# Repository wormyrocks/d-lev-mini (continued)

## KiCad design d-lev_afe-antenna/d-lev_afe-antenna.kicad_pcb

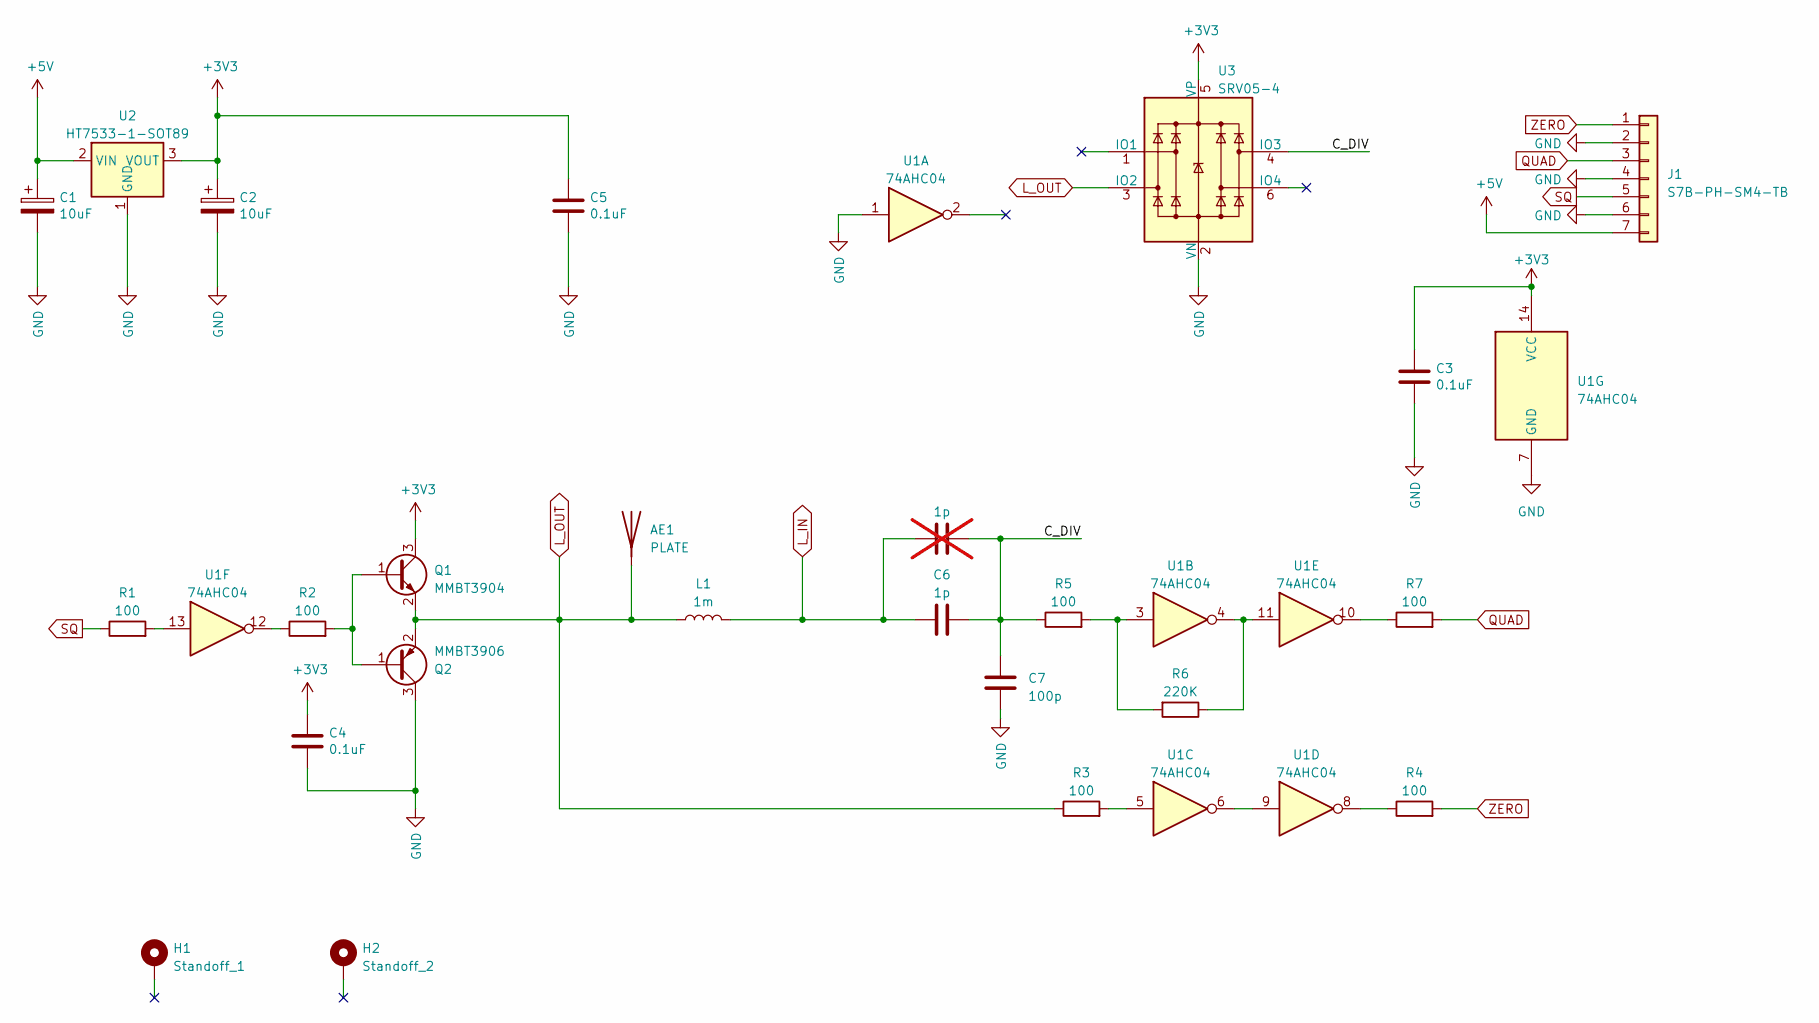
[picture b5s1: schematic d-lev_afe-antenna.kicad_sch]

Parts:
AE1: PLATE
C1, C2: 10uF; CP_EIA-3216-18_Kemet-A
C3, C4, C5: 0.1uF; C_0603_1608Metric
C6: 1p; C_0603_1608Metric
C7: 100p; C_0603_1608Metric
C8: 1p; C_0805_2012Metric_Pad1.18x1.45mm_HandSolder; not fitted
H1: Standoff_1; SMTSO-M4
H2: Standoff_2; SMTSO-M4
J1: S7B-PH-SM4-TB; JST_PH_S7B-PH-SM4-TB_1x07-1MP_P2.00mm_Horizontal
L1: 1m; LargeHoneycombCoil
Q1: MMBT3904; SOT-23
Q2: MMBT3906; SOT-23
R1, R2, R3, R4, R5, R7: 100; R_0603_1608Metric
R6: 220K; R_0603_1608Metric
U1: 74AHC04; SOIC-14_3.9x8.7mm_P1.27mm
U2: HT7533-1-SOT89; SOT-89-3
U3: SRV05-4; SOT-23-6

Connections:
+3V3: C2.1, C3.1, C4.1, C5.1, Q1.3 (C), U1.14 (VCC), U2.3 (VOUT), U3.5 (VP)
+5V: C1.1, J1.7, U2.2 (VIN)
/C_DIV: C6.2, C7.1, C8.2, R5.1, U3.4 (IO3)
GND: C1.2, C2.2, C3.2, C4.2, C5.2, C7.2, J1.2, J1.4, J1.6, Q2.3 (C), U1.1, U1.7 (GND), U2.1 (GND), U3.2 (VN)
L_IN: C6.1, C8.1, L1.2
L_OUT: AE1.1, L1.1, Q1.2 (E), Q2.2 (E), R3.1, U3.3 (IO2)
unnamed: Q1.1 (B), Q2.1 (B), R2.2
unnamed: R1.2, U1.13
unnamed: R2.1, U1.12
unnamed: R3.2, U1.5
unnamed: R4.1, U1.8
unnamed: R5.2, R6.2, U1.3
unnamed: R6.1, U1.4, U1.11
unnamed: R7.1, U1.10
unnamed: U1.6, U1.9
QUAD: J1.3, R7.2
SQ: J1.5, R1.1
ZERO: J1.1, R4.2

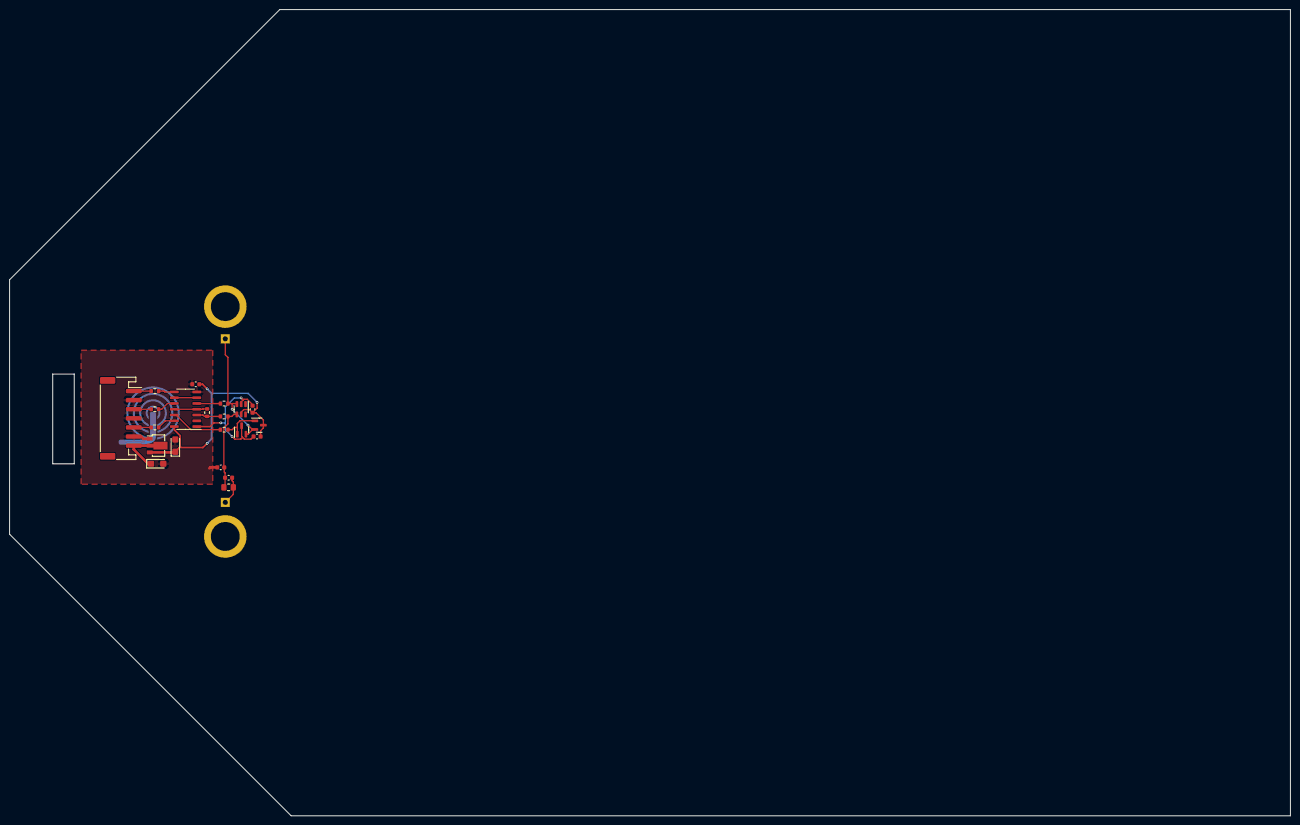
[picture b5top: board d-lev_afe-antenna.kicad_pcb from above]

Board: 2 copper layers, 282.0 x 177.5 mm, 24 parts (1 on the bottom side), 18 nets.

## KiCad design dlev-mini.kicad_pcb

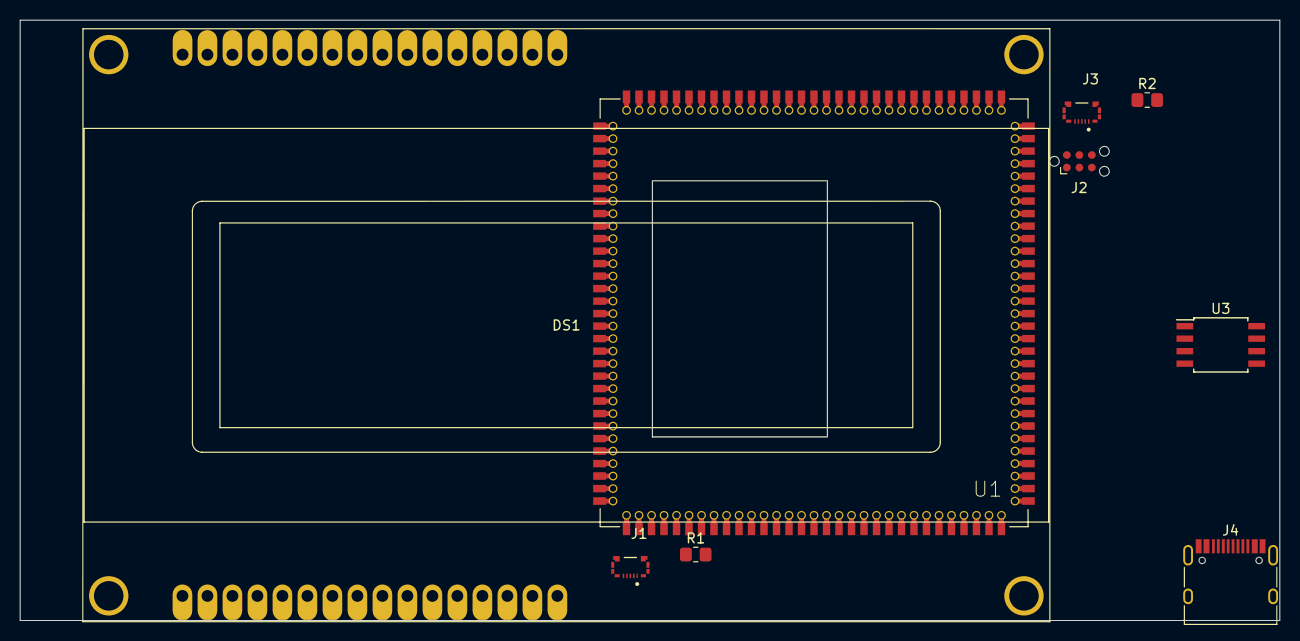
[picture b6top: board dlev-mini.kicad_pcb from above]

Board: 2 copper layers, 128.0 x 61.0 mm, 9 parts (0 on the bottom side), 13 nets, no tracks yet.

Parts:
DS1: LCD-20X4B; ERM2004-1
J1, J3: 20854-005E-02; I-PEX_20854-005E-02
J2: Tag-Connect TC2030-NL; Tag-Connect_TC2030-IDC-NL_2x03_P1.27mm_Vertical
J4: USB_C_Receptacle_USB2.0; USB_C_Receptacle_HRO_TYPE-C-31-M-12
R1, R2: 5.1k; R_0805_2012Metric_Pad1.20x1.40mm_HandSolder
U1: AC608; ac608
U3: 25LCxxx; SOIC-8W_5.3x5.3mm_P1.27mm

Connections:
+2V5: J2.1, U1.63 (VDD2.5)
+3V3: U1.14 (VDD3.3), U1.48 (VDD3.3), U1.78 (VDD3.3), U1.106 (VDD3.3)
+5V: J1.1, J3.1
/AC608/TCK: J2.4, U1.60 (TCK)
/AC608/TDI: J2.3, U1.61 (TDI)
/AC608/TDO: J2.6, U1.64 (TDO)
/AC608/TMS: J2.2, U1.62 (TMS)
GND: J1.5, J1.S1 (SHIELD), J1.S2 (SHIELD), J1.S3 (SHIELD), J1.S4 (SHIELD), J1.S5 (SHIELD), J1.S6 (SHIELD), J1.S7 (SHIELD), J1.S8 (SHIELD), J2.5, J3.5, J3.S1 (SHIELD), J3.S2 (SHIELD), J3.S3 (SHIELD), J3.S4 (SHIELD), J3.S5 (SHIELD), J3.S6 (SHIELD), J3.S7 (SHIELD), J3.S8 (SHIELD), J4.A1 (GND), J4.A12 (GND), J4.B1 (GND), J4.B12 (GND), J4.S1 (SHIELD), R1.1, R2.1, U1.15 (GND), U1.49 (GND), U1.73 (GND), U1.79 (GND), U1.107 (GND)
unnamed: J4.A4 (VBUS), J4.A9 (VBUS), J4.B4 (VBUS), J4.B9 (VBUS)
unnamed: J4.A5 (CC1), R1.2
unnamed: J4.A6 (D+), J4.B6 (D+)
unnamed: J4.A7 (D-), J4.B7 (D-)
unnamed: J4.B5 (CC2), R2.2

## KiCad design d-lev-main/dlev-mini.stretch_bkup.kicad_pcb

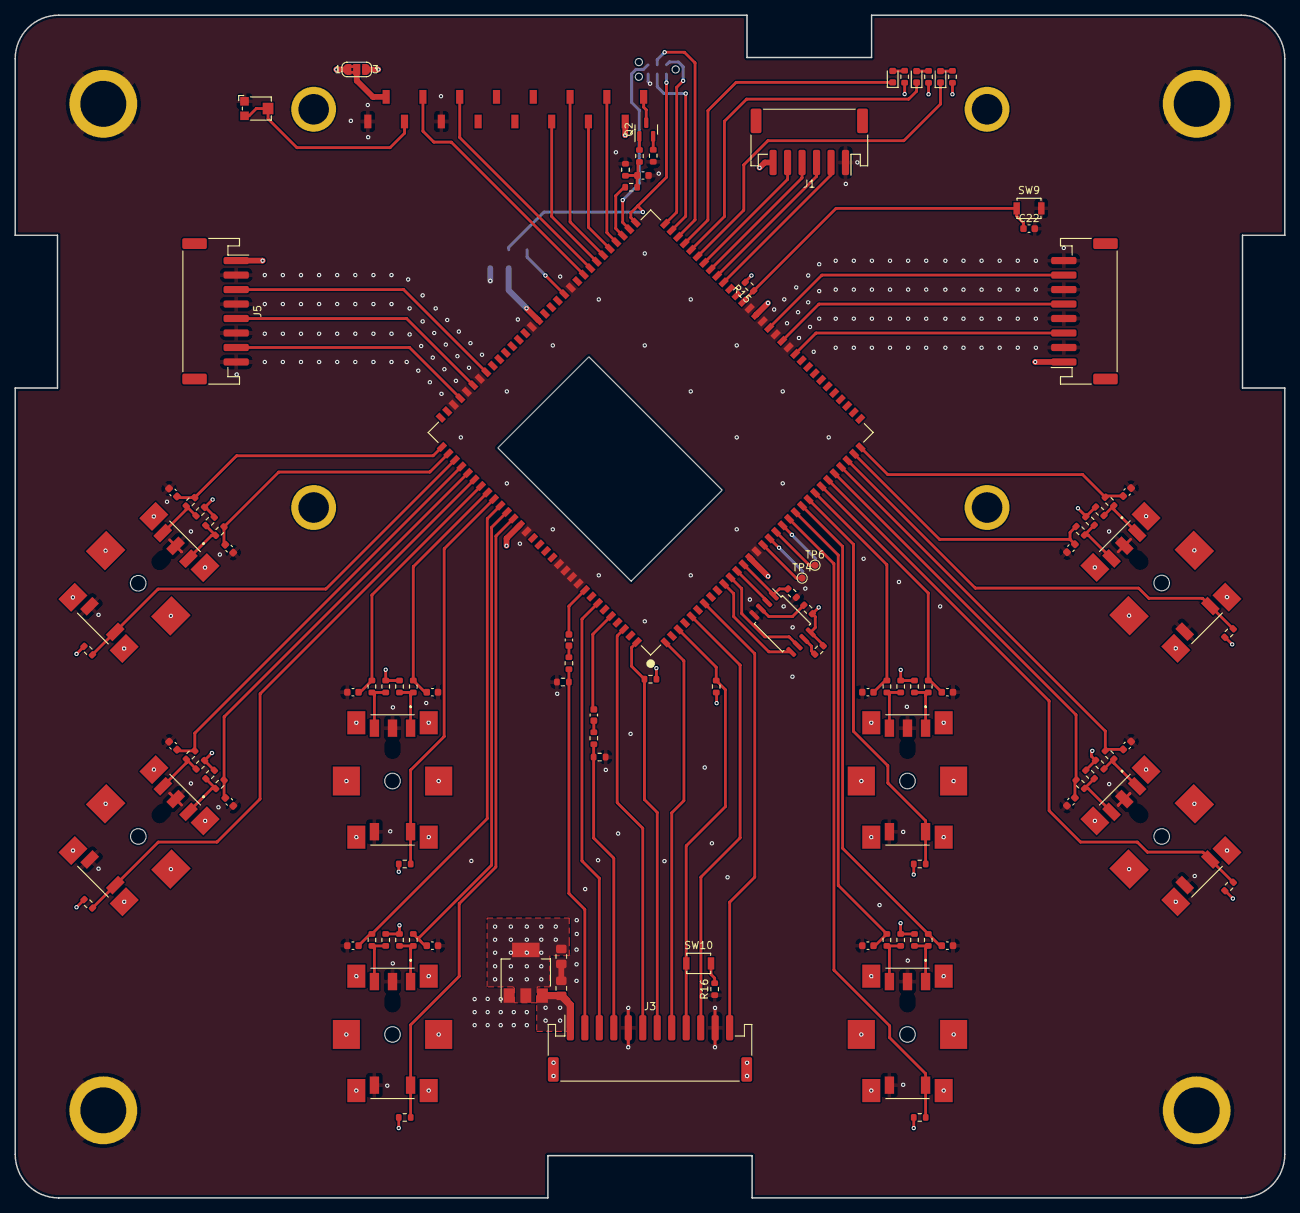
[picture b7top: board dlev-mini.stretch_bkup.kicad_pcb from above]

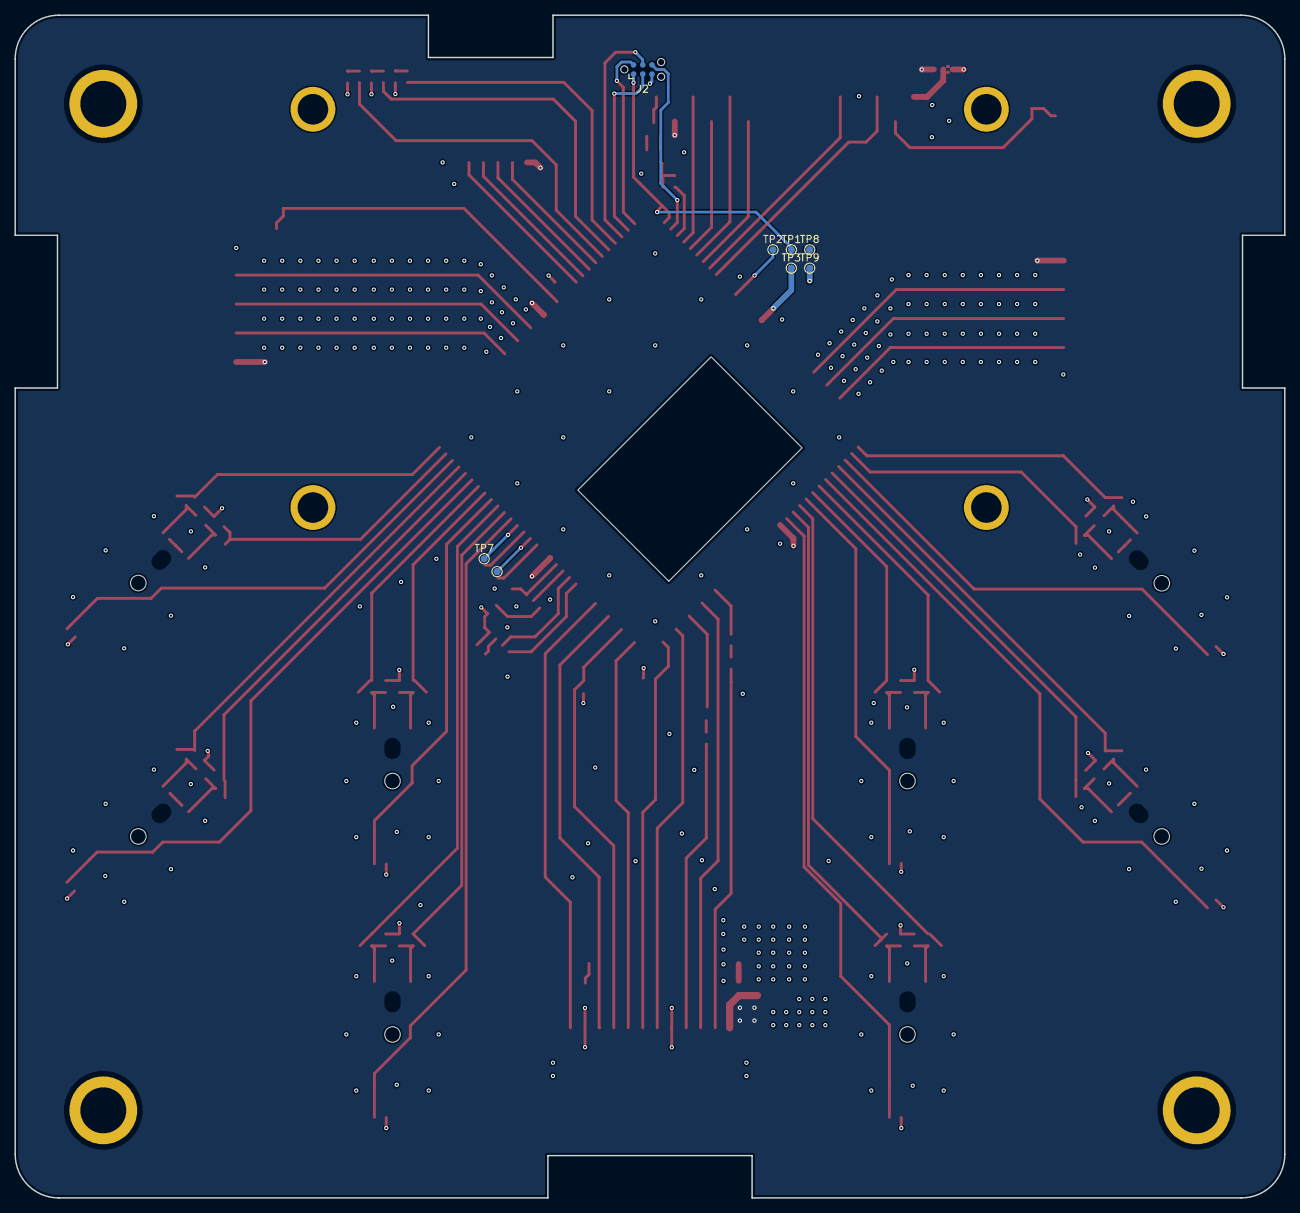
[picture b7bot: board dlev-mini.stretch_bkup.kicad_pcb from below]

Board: 4 copper layers, 175.3 x 163.3 mm, 122 parts (8 on the bottom side), 103 nets.

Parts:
C1, C2, C3, C4, C5, C6, C7, C8, C9, C10, C11, C12, C13, C14, C15, C16, C19, C20, C22: .01u; C_0603_1608Metric
C17, C18: 22u; C_0805_2012Metric_Pad1.18x1.45mm_HandSolder
C21: .1u; C_0603_1608Metric
D1, D2, D3: LED; LED_0603_1608Metric
DS2: LCD-20X4B-noshield; ERM2004-2
H1, H2, H3, H4: MountingHole_Pad; SMTSO-M4
H5, H6, H7, H8: M3 Standoff; SMTSO-M3
J1: S6B-PH-SM4-TB; JST_PH_S6B-PH-SM4-TB_1x06-1MP_P2.00mm_Horizontal
J2: Tag-Connect TC2030-NL; Tag-Connect_TC2030-IDC-NL_2x03_P1.27mm_Vertical
J3: S12B-PH-SM4-TB; JST_PH_S12B-PH-SM4-TB_1x12-1MP_P2.00mm_Horizontal
J4, J5: S8B-PH-SM4-TB; JST_PH_S8B-PH-SM4-TB_1x08-1MP_P2.00mm_Horizontal
JP1: LCD_VSEL; SolderJumper-3_P1.3mm_Bridged2Bar12_RoundedPad1.0x1.5mm_Num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
Q2: MMBT3904; SOT-23
R1, R2, R3, R4, R13, R14, R15, R17, R25, R26, R27, R28, R29, R30, R31, R32, R33, R34, R35, R36, R37, R38, R39, R40, R41, R42, R43, R44, R45, R46, R47, R48, R49, R50, R51, R52, R53, R54, R55, R56, R57, R58, R59, R60, R61, R62: 10k; R_0603_1608Metric
R5, R7, R8, R16, R66, R67, R68: 1k; R_0603_1608Metric
R6: 22; R_0603_1608Metric
R9, R10, R11, R12: 470; R_0603_1608Metric
RV1: 10K; Potentiometer_Bourns_TC33X_Vertical
SW1, SW2, SW3, SW4, SW5, SW6, SW7, SW8: RotaryEncoder_Switch; PEC11S-929K
SW9, SW10: SW_Push; SW_SPST_B3U-1000P
TP1: 2v5; TestPoint_Pad_D1.0mm
TP2: 1v2; TestPoint_Pad_D1.0mm
TP3: 3v3; TestPoint_Pad_D1.0mm
TP4: GPIO_O3; TestPoint_Pad_D1.0mm
TP5: GPIO_O2; TestPoint_Pad_D1.0mm
TP6: GPIO_I3; TestPoint_Pad_D1.0mm
TP7: GPIO_I2; TestPoint_Pad_D1.0mm
TP8: VDD; TestPoint_Pad_D1.0mm
TP9: GND; TestPoint_Pad_D1.0mm
U2: 25LCxxx; SOIC-8_5.275x5.275mm_P1.27mm
U3: AC608; ac608-toponly
U4: AMS1117-3.3; SOT-223-3_TabPin2

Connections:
+2V5: J2.1, TP1.1, U3.63 (VDD2.5)
+3V3: C17.1, JP1.1 (A), R2.2, R3.2, R4.1, R13.1, R14.1, R15.2, R17.1, R25.1, R26.1, R27.1, R28.1, R29.1, R30.1, R31.1, R32.1, R33.1, R34.1, R35.1, R36.1, R37.1, R38.1, R55.1, R56.1, R57.1, R58.1, R59.1, R60.1, R61.1, R62.1, R66.2, R67.2, R68.2, TP3.1, U2.8 (VCC), U3.14 (VDD3.3), U3.48 (VDD3.3), U3.78 (VDD3.3), U3.106 (VDD3.3), U4.2 (VO)
/FPGA/TCK: J2.4, U3.60 (TCK)
/FPGA/TDI: J2.3, U3.61 (TDI)
/FPGA/TDO: J2.6, U3.64 (TDO)
/FPGA/TMS: J2.2, U3.62 (TMS)
/FPGA/enc_1.a: C4.1, R48.1, U3.95 (LVDS_TX4_P)
/FPGA/enc_1.b: C3.1, R40.1, U3.94 (LVDS_TX4_N)
/FPGA/enc_1.s: R56.2, SW2.S1, U3.96 (LVDS_TX5_N)
/FPGA/enc_2.a: C2.1, R47.1, U3.98 (IO_R1)
/FPGA/enc_2.b: C1.1, R39.1, U3.97 (LVDS_TX5_P)
/FPGA/enc_2.s: R55.2, SW1.S1, U3.99 (IO_T2)
/FPGA/enc_3.a: C6.1, R49.1, U3.101 (IO_T3)
/FPGA/enc_3.b: C5.1, R41.1, U3.100 (IO_R3)
/FPGA/enc_3.s: R57.2, SW3.S1, U3.102 (IO_R4)
/FPGA/enc_4.a: C8.1, R50.1, U3.104 (IO_R5)
/FPGA/enc_4.b: C7.1, R42.1, U3.103 (IO_T4)
/FPGA/enc_4.s: R58.2, SW4.S1, U3.105 (IO_T5)
/FPGA/enc_5.a: C10.1, R51.1, U3.31 (IO_D15)
/FPGA/enc_5.b: C9.1, R43.1, U3.30 (IO_D16)
/FPGA/enc_5.s: R59.2, SW5.S1, U3.29 (I_E16)
/FPGA/enc_6.a: C14.1, R53.1, U3.28 (IO_F15)
/FPGA/enc_6.b: C13.1, R45.1, U3.27 (IO_G15)
/FPGA/enc_6.s: R61.2, SW7.S1, U3.26 (IO_F16)
/FPGA/enc_7.a: C16.1, R54.1, U3.25 (IO_K15)
/FPGA/enc_7.b: C15.1, R46.1, U3.24 (IO_J14)
/FPGA/enc_7.s: R62.2, SW8.S1, U3.23 (IO_L14)
/FPGA/enc_8.a: C12.1, R52.1, U3.22 (IO_J16)
/FPGA/enc_8.b: C11.1, R44.1, U3.21 (IO_J15)
/FPGA/enc_8.s: R60.2, SW6.S1, U3.20 (IO_K16)
/FPGA/gpio_i2: TP7.1, U3.19 (IO_L13)
/FPGA/gpio_i3: TP6.1, U3.18 (IO_N14)
/FPGA/gpio_o2: TP5.1, U3.17 (IO_P14)
/FPGA/gpio_o3: TP4.1, U3.16 (IO_N12)
/FPGA/lcd.data0: DS2.11 (DB4), U3.69 (IO_N5)
/FPGA/lcd.data1: DS2.12 (DB5), U3.68 (IO_N3)
/FPGA/lcd.data2: DS2.13 (DB6), U3.67 (IO_M6)
/FPGA/lcd.data3: DS2.14 (DB7), U3.66 (IO_L4)
/FPGA/lcd.e: DS2.6 (E), U3.70 (IO_P3)
/FPGA/lcd.pwm: R8.1, U3.65 (IO_K5)
/FPGA/lcd.rs: DS2.4 (RS), U3.71 (IO_L7)
/FPGA/led1: D1.1 (K), U3.57 (IO_G5)
/FPGA/led2: D2.1 (K), U3.58 (IO_G2)
/FPGA/led3: D3.1 (K), U3.59 (IO_G1)
/FPGA/mem_spi.cl: U2.6 (SCK), U3.11 (IO_L16)
/FPGA/mem_spi.cs: R1.1, U2.1 (~CS), U3.13 (IO_N11)
/FPGA/mem_spi.di: U2.5 (MOSI), U3.10 (IO_L15)
/FPGA/mem_spi.do: U2.2 (MISO), U3.12 (IO_P11)
/FPGA/pitch.quad: J5.3, U3.86 (LVDS_TX1_N)
/FPGA/pitch.sq: J5.5, U3.88 (LVDS_TX2_N)
/FPGA/pitch.zero: J5.7, U3.90 (LVDS_TX3_N)
/FPGA/tuner.le: J1.3, U3.54 (IO_F3)
/FPGA/tuner.oe: J1.2, U3.53 (IO_D1)
/FPGA/tuner.scl: J1.5, U3.56 (IO_F1)
/FPGA/tuner.sda: J1.4, U3.55 (IO_F2)
/FPGA/vol.quad: J4.3, U3.42 (I_A9)
/FPGA/vol.sq: J4.5, U3.44 (IO_C9)
/FPGA/vol.zero: J4.7, U3.46 (IO_D9)
/FPGA/~reset: C22.1, R15.1, SW9.1, U3.50 (I_E1)
/LCD/VLCD: DS2.2 (VDD), JP1.2 (C)
/LCD/backlight_cathode: DS2.16 (K), Q2.3 (C)
/encoder1/A1: R4.2, R47.2, SW1.A
/encoder1/B1: R31.2, R39.2, SW1.B
/encoder2/A1: R25.2, R49.2, SW3.A
/encoder2/B1: R33.2, R41.2, SW3.B
/encoder3/A1: R26.2, R50.2, SW4.A
/encoder3/B1: R34.2, R42.2, SW4.B
/encoder4/A1: R27.2, R51.2, SW5.A
/encoder4/B1: R35.2, R43.2, SW5.B
/encoder5/A1: R29.2, R53.2, SW7.A
/encoder5/B1: R37.2, R45.2, SW7.B
/encoder6/A1: R30.2, R54.2, SW8.A
/encoder6/B1: R38.2, R46.2, SW8.B
/encoder7/A1: R28.2, R52.2, SW6.A
/encoder7/B1: R36.2, R44.2, SW6.B
/encoder/A1: R13.2, R48.2, SW2.A
/encoder/B1: R32.2, R40.2, SW2.B
/spdif_tx_0: C19.1, U3.120 (IO_R12)
/spdif_tx_1: C20.1, U3.116 (IO_R10)
GND: C1.2, C2.2, C3.2, C4.2, C5.2, C6.2, C7.2, C8.2, C9.2, C10.2, C11.2, C12.2, C13.2, C14.2, C15.2, C16.2, C17.2, C18.2, C21.2, C22.2, DS2.1 (VSS), DS2.5 (R/W), H1.1, H2.1, H3.1, H4.1, J1.1, J2.5, J3.5, J3.11, J4.2, J4.4, J4.6, J4.8, J5.2, J5.4, J5.6, J5.8, R1.2, R6.1, R7.1, R11.1, R12.1, R16.1, RV1.1, SW1.C, SW1.S2, SW2.C, SW2.S2, SW3.C, SW3.S2, SW4.C, SW4.S2, SW5.C, SW5.S2, SW6.C, SW6.S2, SW7.C, SW7.S2, SW8.C, SW8.S2, SW9.2, TP9.1, U2.4 (GND), U3.15 (GND), U3.43 (I_B9), U3.45 (I_A8), U3.47 (I_B8), U3.49 (GND), U3.73 (GND), U3.79 (GND), U3.87 (LVDS_TX1_P), U3.89 (LVDS_TX2_P), U3.91 (LVDS_TX3_P), U3.107 (GND), U3.112 (I_R8), U3.113 (I_T8), U3.114 (I_R9), U3.115 (I_T9), U4.1 (GND)
unnamed: C19.2, R10.1
unnamed: C20.2, R9.1
unnamed: C21.1, R5.1, R7.2, R8.2
unnamed: D1.2 (A), R66.1
unnamed: D2.2 (A), R67.1
unnamed: D3.2 (A), R68.1
unnamed: DS2.3 (V0), RV1.2, RV1.3
unnamed: Q2.1 (B), R5.2
unnamed: Q2.2 (E), R6.2
unnamed: R16.2, SW10.2
unnamed: R3.1, U2.7 (~HOLD)
unnamed: R2.1, U2.3 (~WP)
unnamed: TP2.1, U3.74 (VDD1.2)
VDD: C18.1, DS2.15 (A), J1.6, J3.1, J4.1, J5.1, JP1.3 (B), TP8.1, U4.3 (VI)
acal_btn: J3.9, R14.2, SW10.1, U3.3 (IO_R16)
midi_in: J3.12, U3.7 (IO_N16)
midi_out: J3.10, U3.5 (IO_P16)
mute_btn: J3.7, R17.2, U3.124 (IO_R14)
mute_led: J3.3, U3.118 (IO_R11)
spdif_line: J3.4, R10.2, R12.2
spdif_mon: J3.2, R9.2, R11.2
uart_rx: J3.8, U3.1 (IO_T14)
uart_tx: J3.6, U3.122 (IO_R13)

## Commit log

2023-02-11 Laid down some ideas
2023-02-13 Add ac608 model and move into subdirectory
2023-02-13 Add AFE antenna schematic and rough layout
2023-02-20 Add block diagram
2023-02-23 Many changes
    Reorganized libraries to share between projects
    Set up JLC 2- and 4- layer design rules
    Finished copying over most of the schematic (excluding I/O board)
2023-02-25 Reorganized, and updates
2023-02-25 Add ess-dac library
2023-02-28 schematic + wiring for avr
2023-02-28 add more datasheets for ESS/ power components
2023-03-02 clean up 3d models
2023-03-08 Level shifters and rearrange encoders
    * WIP: use net buses more effectively to organize encoder signals
    * Add application note for level shifters
    * Add level shifters for UART, change MIDI level shifter BJT to FET
    * Add MIDI_HI pull-up on d-lev-io board
    * Add/change some footprints
2023-03-08 more encoder bus mangling
2023-03-09 Small changes to 3D models and footprints; fixed bus routing of encoder signals
2023-03-09 Moved encoders around
2023-03-12 start routing
    * add simple knob model
    * place encoders
    * change display to use SMT female headers and SMTSO screw holes
    * rotate fpga model 90 degrees
2023-03-12 many changes to pcb
2023-03-12 knob.scad changes, not happy with them yet
2023-03-14 Switch from Rpacks to 0603 pull resistors
2023-03-15 more minor pusharounds and updates
2023-03-15 Fix error in pinmap spreadsheet
2023-03-15 Pinned out FPGA and rearranged encoders again
2023-03-15 Built out power circuitry on d-lev-io
2023-03-16 mostly done routing
2023-03-16 four layer routes
2023-03-16 Clean up unroutes and add DRC
2023-03-17 main board - push vias around
2023-03-18 Improve routing and rearrange I/O connector
2023-03-18 messed up line endings
2023-03-24 Add buck converter schematic
2023-03-24 Add footprint references and fix error in buck schematic
2023-03-24 Via stitching around afe traces and add fix for lcd contrast pot
2023-04-07 many many changes'
2023-04-12 many more changes
2023-04-13 map SAMD21 pins
2023-04-14 Add gerbers for 9016K2M EVB
2023-04-14 Added DAC schematic to I/O board
2023-04-15 updated library files
2023-04-15 add headphone amp
2023-04-15 round tracks and teardrops
2023-04-15 add more datasheets
2023-04-15 Add Coilcraft SMT inductor footprints
2023-04-15 Aesthetic improvements to main/AFE
2023-04-15 more aesthetics
2023-04-17 io board more analog schematic capture
2023-04-17 assign vol pot to analog pin
2023-04-21 many board updates
2023-04-21 more routing
2023-04-27 Routed IO board
2023-04-27 add 5-pin CV expansion header
2023-04-27 Moved datasheets out of d-lev-dac and deleted
2023-04-27 route cv header
2023-05-03 Add tuner
2023-05-04 I/O board silk placement
2023-05-04 refdes font
2023-05-10 finished routing tuner
2023-05-10 Add burn list / to-dos
2023-05-11 tuner: fix led footprints, reroute, place vias artistically
2023-05-11 d-lev-io: de-rounded tracks
2023-05-11 d-lev-main: de-round tracks
2023-05-11 d-lev-afe: de-rounded traces
2023-05-11 renamed dlev-mini to d-lev-main
2023-05-11 scripts: began writing gerbolyzer
2023-05-11 d-lev-main: clean up silkscreen refdes'
2023-05-12 gerbolyze scripts
2023-05-12 all boards: fix some 3d model paths
2023-05-13 d-lev-io: pass drc before rounding traces
2023-05-13 drc improvements
2023-05-14 tuner: fixed led footprints
2023-05-14 star pattern done
2023-05-14 tuner: pass drc
2023-05-15 everything passes drc as much as i care for it to, added silk art
2023-05-15 all design files updated with current contents of jlc cart
2023-05-17 Add JLC releases
2023-06-06 Add iBOMs and additional part numbers
2023-06-06 Add display-shim adapter board
2023-06-12 add .gitattributes
2023-06-12 Normalize line endings
2023-07-21 cleaned up extraneous datasheets
2023-08-20 Added step file of the entire enclosure assembly
2023-08-21 d-lev-afe: switch to 2 layers, add 'antenna' version, pick out JLC parts
2023-10-17 pushed smaller AFE board
